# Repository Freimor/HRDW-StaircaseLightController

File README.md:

# HRDW-StaircaseLightController
A modular staircase LED light controller based on Raspberry Pico

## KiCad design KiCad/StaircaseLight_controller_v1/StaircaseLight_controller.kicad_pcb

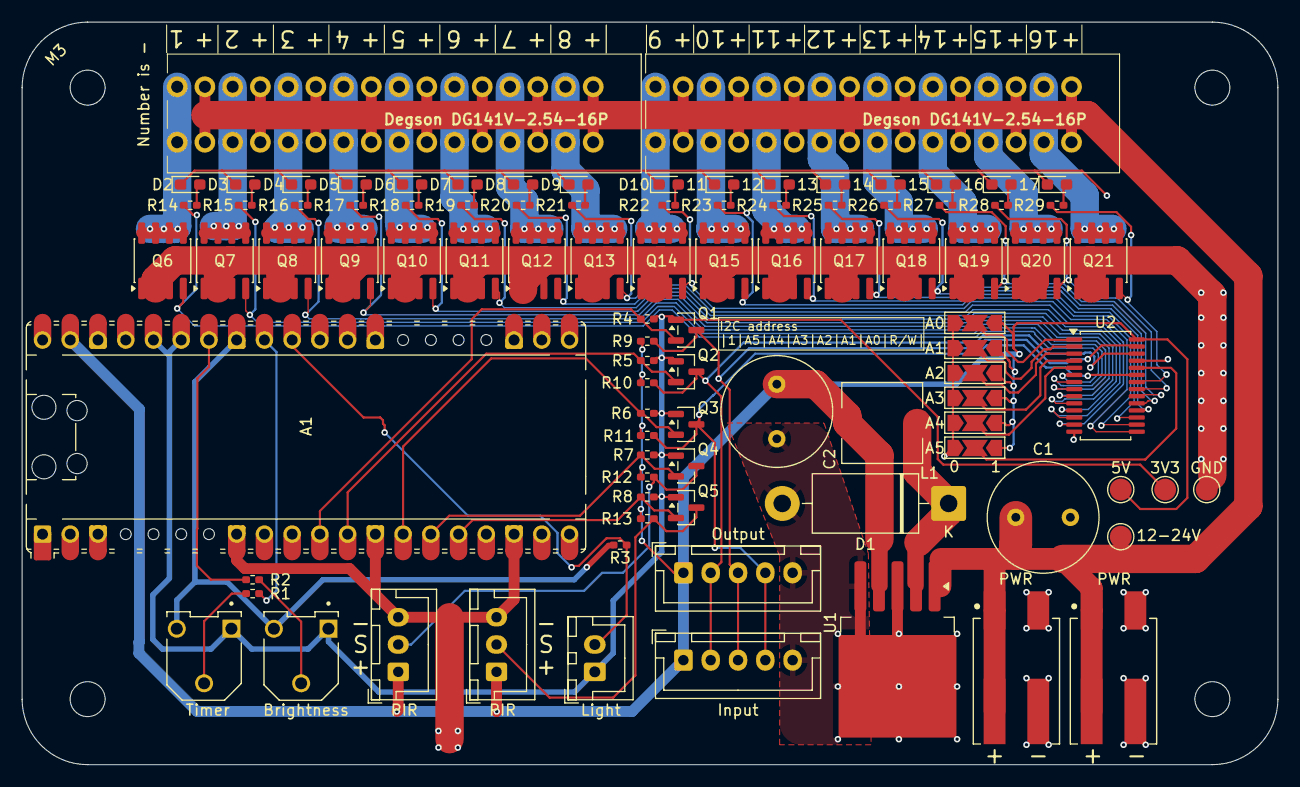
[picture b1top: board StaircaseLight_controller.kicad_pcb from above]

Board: 2 copper layers, 115.0 x 68.0 mm, 95 parts (0 on the bottom side), 75 nets.

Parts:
3V3: 3v3; TestPoint_Pad_D2.0mm
5V: 5v; TestPoint_Pad_D2.0mm
11, 12, 13, 14, 15, 16, 17: LED; LED_0603_1608Metric_Pad1.05x0.95mm_HandSolder
12-24V: VDD; TestPoint_Pad_D2.0mm
A1: RaspberryPi_Pico; RaspberryPi_Pico_Common_Unspecified
Brightness: POT_Brightness; POT_BOURNS_3306F
C1: 330uF 50v; C_Radial_D10.0mm_H16.0mm_P5.00mm
C2: 220uF 10v; C_Radial_D10.0mm_H12.5mm_P5.00mm
D1: 1N5822; D_DO-201AD_P15.24mm_Horizontal
D2, D3, D4, D5, D6, D7, D8, D9, D10: LED; LED_0603_1608Metric_Pad1.05x0.95mm_HandSolder
GND: GND; TestPoint_Pad_D2.0mm
Input: BOARD_IN; JST_XH_B5B-XH-A_1x05_P2.50mm_Vertical
J4: ROW1; Conn_Degson_DG141V-2.54-16P
J6: ROW2; Conn_Degson_DG141V-2.54-16P
JP1: ADD_5; SolderJumper-3_P2.0mm_Open_TrianglePad1.0x1.5mm_NumberLabels
JP2: ADD_4; SolderJumper-3_P2.0mm_Open_TrianglePad1.0x1.5mm_NumberLabels
JP3: ADD_3; SolderJumper-3_P2.0mm_Open_TrianglePad1.0x1.5mm_NumberLabels
JP4: ADD_2; SolderJumper-3_P2.0mm_Open_TrianglePad1.0x1.5mm_NumberLabels
JP5: ADD_1; SolderJumper-3_P2.0mm_Open_TrianglePad1.0x1.5mm_NumberLabels
JP6: ADD_0; SolderJumper-3_P2.0mm_Open_TrianglePad1.0x1.5mm_NumberLabels
L1: 47uH (or 100uH from graph); L_7.3x7.3_H4.5
Light: Photo; JST_XH_B2B-XH-A_1x02_P2.50mm_Vertical
M3: MountingHole_3.2mm_M3
Output: BOARD_OUT; JST_XH_B5B-XH-A_1x05_P2.50mm_Vertical
PIR: PIR_2_conn; JST_XH_B3B-XH-A_1x03_P2.50mm_Vertical
PIR#2: PIR_1_conn; JST_XH_B3B-XH-A_1x03_P2.50mm_Vertical
PWR: PWR_IN; Conn_WAGO_2060-402
PWR#2: PWR_SLV; Conn_WAGO_2060-402
Q1, Q2, Q3, Q4, Q5: BSS138 (or AO3400); SOT-23
Q6, Q7, Q8, Q9, Q10, Q11, Q12, Q13, Q14, Q15, Q16, Q17, Q18, Q19, Q20, Q21: AO4466; SOP-8_3.76x4.96mm_P1.27mm
R1, R2, R14, R15, R16, R17, R18, R19, R20, R21, R22, R23, R24, R25, R26, R27, R28, R29: 1k; R_0402_1005Metric_Pad0.72x0.64mm_HandSolder
R3, R11, R12, R13: 10k; R_0402_1005Metric_Pad0.72x0.64mm_HandSolder
R4, R5: 1.8K; R_0402_1005Metric_Pad0.72x0.64mm_HandSolder
R6, R7, R8: 10K; R_0402_1005Metric_Pad0.72x0.64mm_HandSolder
R9, R10: 1.8k; R_0402_1005Metric_Pad0.72x0.64mm_HandSolder
Timer: POT_Timer; POT_BOURNS_3306F
U1: LM2575-5.0BU; TO-263-5_TabPin3
U2: PCA9685PW; TSSOP-28_4.4x9.7mm_P0.65mm

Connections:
12-24V: 12-24V.1, C1.1, J4.2, J4.4, J4.6, J4.8, J4.10, J4.12, J4.14, J4.16, J6.2, J6.4, J6.6, J6.8, J6.10, J6.12, J6.14, J6.16, PWR.1, PWR#2.1, U1.1 (VIN)
+3.3V: 3V3.1, A1.35 (ADC_VREF), A1.36 (3V3), Brightness.1, Light.1, Q1.1 (G), Q2.1 (G), Q3.1 (G), Q4.1 (G), Q5.1 (G), R4.2, R5.2, R6.2, R7.2, R8.2, Timer.1
+5V: 5V.1, A1.39 (VSYS), C2.1, Input.1, JP1.3 (B), JP2.3 (B), JP3.3 (B), JP4.3 (B), JP5.3 (B), JP6.3 (B), L1.2, Output.1, PIR.1, PIR#2.1, R9.2, R10.2, R11.2, R12.2, R13.2, U1.4 (FB), U2.28 (VDD)
GND: 11.1 (K), 12.1 (K), 13.1 (K), 14.1 (K), 15.1 (K), 16.1 (K), 17.1 (K), A1.3 (GND), A1.8 (GND), A1.13 (GND), A1.18 (GND), A1.23 (GND), A1.28 (GND), A1.38 (GND), C1.2, C2.2, D1.2 (A), D2.1 (K), D3.1 (K), D4.1 (K), D5.1 (K), D6.1 (K), D7.1 (K), D8.1 (K), D9.1 (K), D10.1 (K), GND.1, Input.5, JP1.1 (A), JP2.1 (A), JP3.1 (A), JP4.1 (A), JP5.1 (A), JP6.1 (A), Output.5, PIR.3, PIR#2.3, PWR.2, PWR#2.2, Q6.1 (S), Q6.2 (S), Q6.3 (S), Q7.1 (S), Q7.2 (S), Q7.3 (S), Q8.1 (S), Q8.2 (S), Q8.3 (S), Q9.1 (S), Q9.2 (S), Q9.3 (S), Q10.1 (S), Q10.2 (S), Q10.3 (S), Q11.1 (S), Q11.2 (S), Q11.3 (S), Q12.1 (S), Q12.2 (S), Q12.3 (S), Q13.1 (S), Q13.2 (S), Q13.3 (S), Q14.1 (S), Q14.2 (S), Q14.3 (S), Q15.1 (S), Q15.2 (S), Q15.3 (S), Q16.1 (S), Q16.2 (S), Q16.3 (S), Q17.1 (S), Q17.2 (S), Q17.3 (S), Q18.1 (S), Q18.2 (S), Q18.3 (S), Q19.1 (S), Q19.2 (S), Q19.3 (S), Q20.1 (S), Q20.2 (S), Q20.3 (S), Q21.1 (S), Q21.2 (S), Q21.3 (S), U1.3 (GND), U1.5 (~ON/OFF), U2.14 (VSS), U2.25 (EXTCLK)
GNDS: A1.33 (AGND), Brightness.3, R3.2, Timer.3
I2C_C_3v3: A1.12 (GPIO9), Q2.2 (S), R5.1
I2C_C_5v: Input.2, Output.2, Q2.3 (D), R10.1, U2.26 (SCL)
I2C_D_3v3: A1.11 (GPIO8), Q1.2 (S), R4.1
I2C_D_5v: Input.3, Output.3, Q1.3 (D), R9.1, U2.27 (SDA)
unnamed: A1.31 (GPIO26_ADC0), Light.2, R3.1
unnamed: A1.32 (GPIO27_ADC1), R1.1
unnamed: A1.34 (GPIO28_ADC2), R2.1
unnamed: D1.1 (K), L1.1, U1.2 (OUT)
unnamed: D2.2 (A), R14.2
unnamed: D3.2 (A), R15.2
unnamed: D4.2 (A), R16.2
unnamed: D5.2 (A), R17.2
unnamed: D6.2 (A), R18.2
unnamed: D7.2 (A), R19.2
unnamed: D8.2 (A), R20.2
unnamed: D9.2 (A), R21.2
unnamed: D10.2 (A), R22.2
unnamed: 11.2 (A), R23.2
unnamed: 12.2 (A), R24.2
unnamed: 13.2 (A), R25.2
unnamed: 14.2 (A), R26.2
unnamed: 15.2 (A), R27.2
unnamed: 16.2 (A), R28.2
unnamed: 17.2 (A), R29.2
unnamed: JP1.2 (C), U2.24 (A5)
unnamed: JP2.2 (C), U2.5 (A4)
unnamed: JP3.2 (C), U2.4 (A3)
unnamed: JP4.2 (C), U2.3 (A2)
unnamed: JP5.2 (C), U2.2 (A1)
unnamed: JP6.2 (C), U2.1 (A0)
unnamed: R1.2, Timer.2
unnamed: Brightness.2, R2.2
PCA9685_OE_3v3: A1.14 (GPIO10), Q3.2 (S), R6.1
PCA9685_OE_5v: Input.4, Output.4, Q3.3 (D), R11.1, U2.23 (~OE)
PIR_1_3v3: A1.15 (GPIO11), Q4.2 (S), R7.1
PIR_1_5v: PIR#2.2, Q4.3 (D), R12.1
PIR_2_3v3: A1.16 (GPIO12), Q5.2 (S), R8.1
PIR_2_5v: PIR.2, Q5.3 (D), R13.1
PORT1: J4.1, Q6.5 (D), Q6.6 (D), Q6.7 (D), Q6.8 (D)
PORT2: J4.3, Q7.5 (D), Q7.6 (D), Q7.7 (D), Q7.8 (D)
PORT3: J4.5, Q8.5 (D), Q8.6 (D), Q8.7 (D), Q8.8 (D)
PORT4: J4.7, Q9.5 (D), Q9.6 (D), Q9.7 (D), Q9.8 (D)
PORT5: J4.9, Q10.5 (D), Q10.6 (D), Q10.7 (D), Q10.8 (D)
PORT6: J4.11, Q11.5 (D), Q11.6 (D), Q11.7 (D), Q11.8 (D)
PORT7: J4.13, Q12.5 (D), Q12.6 (D), Q12.7 (D), Q12.8 (D)
PORT8: J4.15, Q13.5 (D), Q13.6 (D), Q13.7 (D), Q13.8 (D)
PORT9: J6.1, Q14.5 (D), Q14.6 (D), Q14.7 (D), Q14.8 (D)
PORT10: J6.3, Q15.5 (D), Q15.6 (D), Q15.7 (D), Q15.8 (D)
PORT11: J6.5, Q16.5 (D), Q16.6 (D), Q16.7 (D), Q16.8 (D)
PORT12: J6.7, Q17.5 (D), Q17.6 (D), Q17.7 (D), Q17.8 (D)
PORT13: J6.9, Q18.5 (D), Q18.6 (D), Q18.7 (D), Q18.8 (D)
PORT14: J6.11, Q19.5 (D), Q19.6 (D), Q19.7 (D), Q19.8 (D)
PORT15: J6.13, Q20.5 (D), Q20.6 (D), Q20.7 (D), Q20.8 (D)
PORT16: J6.15, Q21.5 (D), Q21.6 (D), Q21.7 (D), Q21.8 (D)
SW1: Q6.4 (G), R14.1, U2.6 (LED0)
SW2: Q7.4 (G), R15.1, U2.7 (LED1)
SW3: Q8.4 (G), R16.1, U2.8 (LED2)
SW4: Q9.4 (G), R17.1, U2.9 (LED3)
SW5: Q10.4 (G), R18.1, U2.10 (LED4)
SW6: Q11.4 (G), R19.1, U2.11 (LED5)
SW7: Q12.4 (G), R20.1, U2.12 (LED6)
SW8: Q13.4 (G), R21.1, U2.13 (LED7)
SW9: Q14.4 (G), R22.1, U2.15 (LED8)
SW10: Q15.4 (G), R23.1, U2.16 (LED9)
SW11: Q16.4 (G), R24.1, U2.17 (LED10)
SW12: Q17.4 (G), R25.1, U2.18 (LED11)
SW13: Q18.4 (G), R26.1, U2.19 (LED12)
SW14: Q19.4 (G), R27.1, U2.20 (LED13)
SW15: Q20.4 (G), R28.1, U2.21 (LED14)
SW16: Q21.4 (G), R29.1, U2.22 (LED15)

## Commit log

2026-04-22 Core
